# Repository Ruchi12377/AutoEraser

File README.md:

# 自動ホワイトボード消しの実用化に向けた改良

## 2022/12/13 第4版発行

---

# 目次

1. はじめに
   
   1. 概要
   
   2. 開発環境
   
   3. システムの概要

2. コンポーネント
   
   1. Camera
   
   2. Image
   
   3. KeystoneCorrection
   
   4. WhiteBoard (Feature)
   
   5. Select
   
   6. Erase (Feature)
   
   7. MoveInitial
   
   8. InitialSetting
   
   9. Pump
   
   10. Move (Feature)
   
   11. Serial

# 1.はじめに

## 1.概要

我々はRTミドルウェアを用いて、ホワイトボードの文字を自動で消すシステムを開発している。本稿では、本システムの改善について述べる。昨年のシステムとの相違点は主に三点ある。一つ目は、材質を木材からアルミニウムに変更することで歪みを解消し、スムーズな可動と軽量化を図ったことである。二つ目は消したい領域をより細かく指定可能にすることで、本来消すべきではない部分を消してしまうことを防げるようになったことである。三つ目は水が入ったタンクを設置し、自動で白板を濡らすことができるようになったため、雑巾を取り外して濡らす必要がなくなったことである。

自動ホワイトボード消しのイメージ

## 2.開発環境

本コンポーネント群の開発環境を以下に示す。

| OS       | Windows10                                 |
| -------- | ----------------------------------------- |
| RTミドルウェア | OpenRTM-aist-2.0.0-RELESE(Python 版)       |
| 開発環境     | VSCode                                    |
| Python   | 3.8.5                                     |
| 必要モジュール  | math, numpy, cv2, PIL, sys, time, tkinter |

## 3.システムの概要

このシステムは、ユーザーの指定した範囲もしくは、全範囲(全部消す)をレールや枠組みに沿って本体が移動し自動でホワイトボードに書かれたものを消すものである。

そして、制御部分にはRTミドルウェアを用いており、Cameraコンポーネントを用いて取得したホワイトボードの動画(画像)をSelectコンポーネントで消す範囲を選択し、Eraseコンポーネントでどのように移動するか決定することでMoveコンポーネントが移動するためのコマンドを生成し、Serialコンポーネントを用いてハードウェアに移動するデータをもちいて実際に動かす。というものである。

以下の2つのコンポーネント図を示す。

1.詳しく説明してあるコンポーネント図

2.簡潔化しまとまりごとに色分けしたコンポーネント図

# 2.コンポーネント

## 1.Camera

カメラから取得した画像を出力するコンポーネント。

コンフィギュレーションから使用するカメラのインデックスを設定することができる。

- **InPort**

- **OutPort**
  
  | **名称** | **データ型**         | **説明**            |
  | ------ | ---------------- | ----------------- |
  | image  | RTC::CameraImage | カメラから取得した画像を出力する。 |

- Configuration
  
  | 名称          | データ型  | 説明                   | 初期値 | 制限      |
  | ----------- | ----- | -------------------- | --- | ------- |
  | CameraIndex | short | 使用するカメラのインデックスを設定する。 | 0   | 0<=x<=5 |

## 2.Image

コンフィギュレーションで指定されたパスの画像をポートから出力するコンポーネント。

デバックする際、Cameraコンポーネントの代わりに使用することを想定している。

- **InPort**

- **OutPort**
  
  | 名称    | データ型             | 説明                           |
  | ----- | ---------------- | ---------------------------- |
  | Image | RTC::CameraImage | コンフィギュレーションで指定されたパスの画像を出力する。 |

- **Configuration**
  
  | 名称   | データ型   | 説明        | 初期値          | 制限        |
  | ---- | ------ | --------- | ------------ | --------- |
  | Path | string | 出力する画像のパス | Emprt String | Undefined |

## 3.KeystoneCorrection

台形補正をするコンポーネント。

GUIに画像が表示されており、4隅をクリックすることで台形補正を行う。

ホワイトボードをカメラで撮影しなぞるようにして選択するが、その際ホワイトボードの画像は斜めになっているのでこのコンポーネントが必要。

- **InPort**

| 名称      | データ型             | 説明        |
| ------- | ---------------- | --------- |
| ImageIn | RTC::CameraImage | 台形補正をする画像 |

- **OutPort**

| 名称       | データ型             | 説明        |
| -------- | ---------------- | --------- |
| ImageOut | RTC::CameraImage | 台形補正済みの画像 |

- **Configuration**

## 4.WhiteBoard (Feature)

実装予定

## 5.Select

範囲選択をし、選択した矩形の座標を出力するコンポーネント。

選択範囲を左上を基準とし0~1で表す。真ん中から右下まで選択した場合、Start = (0.5, 0.5) End = (1, 1)となる。

**Camera** **Image** **Select** の3つに加え画像切り取りコンポーネントを作成することで画像切り取りができるコンポーネント群をかんたんに作れる。

- **InPort**
  
  | 名称            | データ型        | 説明          |
  | ------------- | ----------- | ----------- |
  | ShowImage     | CameraImage | 選択する際の背景の画像 |
  | CompeteMotion | TimedString | 終了した動作名     |
  | StatusCode    | TimedUShort | ステータスコード    |

- **OutPort**
  
  | 名称       | データ型              | 説明         |
  | -------- | ----------------- | ---------- |
  | StartPos | RTC::TimedPoint2D | 指定された範囲の始点 |
  | EndPos   | RTC::TimedPoint2D | 指定された範囲の終点 |

- **Configuration**
  
  | 名称     | データ型 | 説明         | 初期値 | 制限           |
  | ------ | ---- | ---------- | --- | ------------ |
  | Width  | int  | 選択ウィンドウの横幅 | 800 | 400<=x<=1600 |
  | Height | int  | 選択ウィンドウの高さ | 450 | 225<=x<=900  |

## 5.Erase (Feature)

選択された範囲を元に消すためのパスを決定するコンポーネント。

- **InPort**
  
  | 名称       | データ型              | 説明         |
  | -------- | ----------------- | ---------- |
  | StartPos | RTC::TimedPoint2D | 指定された範囲の始点 |
  | EndPos   | RTC::TimedPoint2D | 指定された範囲の終点 |

- **OutPort**
  
  | 名称       | データ型           | 説明                         |
  | -------- | -------------- | -------------------------- |
  | MovePath | TimedStringSeq | **x:y**の形式で移動する座標のデータを出力する |

- **Configuration**
  
  | 名称  | データ型 | 説明  | 初期値 | 制限  |
  | --- | ---- | --- | --- | --- |
  |     |      |     |     |     |

## 5.MoveInitial

初期位置(左上)に本体を移動させるコンポーネント。

移動しきったかの検出にはリミットスイッチを用いる。

- **InPort**
  
  | 名称            | データ型      | 説明              |
  | ------------- | --------- | --------------- |
  | MoveToInitial | RTC::Time | 初期位置に戻るタイミングを指定 |

- **OutPort**
  
  | 名称      | データ型             | 説明                |
  | ------- | ---------------- | ----------------- |
  | Command | RTC::TimedString | 初期位置に戻るためのコマンドを生成 |

- **Configuration**
  
  | 名称      | データ型 | 説明               | 初期値 | 制限        |
  | ------- | ---- | ---------------- | --- | --------- |
  | TimeOut | int  | 移動完了せずタイムアウトする時間 | -1  | -1<=x<=60 |

## 6.InitialSetting

本体のサイズ、ホワイトボードの横幅をリミットスイッチを用いて検出するコンポーネント。

単位はステッピングモーターの回転数。

- **InPort**
  
  | 名称      | データ型      | 説明        |
  | ------- | --------- | --------- |
  | Setting | RTC::Time | 検出するタイミング |

- **OutPort**
  
  | 名称      | データ型             | 説明                |
  | ------- | ---------------- | ----------------- |
  | Command | RTC::TimedString | 初期設定を行うためのコマンドを生成 |

- **Configuration**
  
  | 名称  | データ型 | 説明  | 初期値 | 制限  |
  | --- | ---- | --- | --- | --- |
  |     |      |     |     |     |

## 7.Pump

指定された量の水をポンプから出すコンポーネント。

単位はmL

- **InPort**
  
  | 名称          | データ型             | 説明         |
  | ----------- | ---------------- | ---------- |
  | WaterAmount | RTC::TimedUShort | ポンプから出す水の量 |

- **OutPort**
  
  | 名称              | データ型             | 説明               |
  | --------------- | ---------------- | ---------------- |
  | PumpWaterAmount | RTC::TimedString | ポンプから水を出すためのコマンド |

- **Configuration**
  
  | 名称   | データ型 | 説明  | 初期値 | 制限  |
  | ---- | ---- | --- | --- | --- |
  | Amou |      |     |     |     |

## 8.Move (Feature)

パスを元に、モーターを動かすためのコマンドを生成するコンポーネント。

- **InPort**
  
  | 名称      | データ型              | 説明            |
  | ------- | ----------------- | ------------- |
  | Command | RTC::TimedPoint2D | モーターを動かすための座標 |

- **OutPort**
  
  | 名称      | データ型             | 説明              |
  | ------- | ---------------- | --------------- |
  | Command | RTC::TimedString | ハードウェアに送信するコマンド |

- **Configuration**
  
  | 名称  | データ型 | 説明  | 初期値 | 制限  |
  | --- | ---- | --- | --- | --- |
  |     |      |     |     |     |

## 9.Serial

シリアル通信のRead/Writeを行うコンポーネント。

- **InPort**
  
  | 名称    | データ型             | 説明             |
  | ----- | ---------------- | -------------- |
  | Write | RTC::TimedString | シリアル通信で書き込むデータ |

- **OutPort**
  
  | 名称   | データ型             | 説明              |
  | ---- | ---------------- | --------------- |
  | Read | RTC::TimedString | シリアル通信で読み込んだデータ |

- **Configuration**
  
  | 名称        | データ型   | 説明               | 初期値         | 制限        |
  | --------- | ------ | ---------------- | ----------- | --------- |
  | Path      | string | シリアル通信を行うデバイスのパス | EmptyString |           |
  | Boundrate | int    | シリアル通信を行うための速度   | 9600        | Undefined |

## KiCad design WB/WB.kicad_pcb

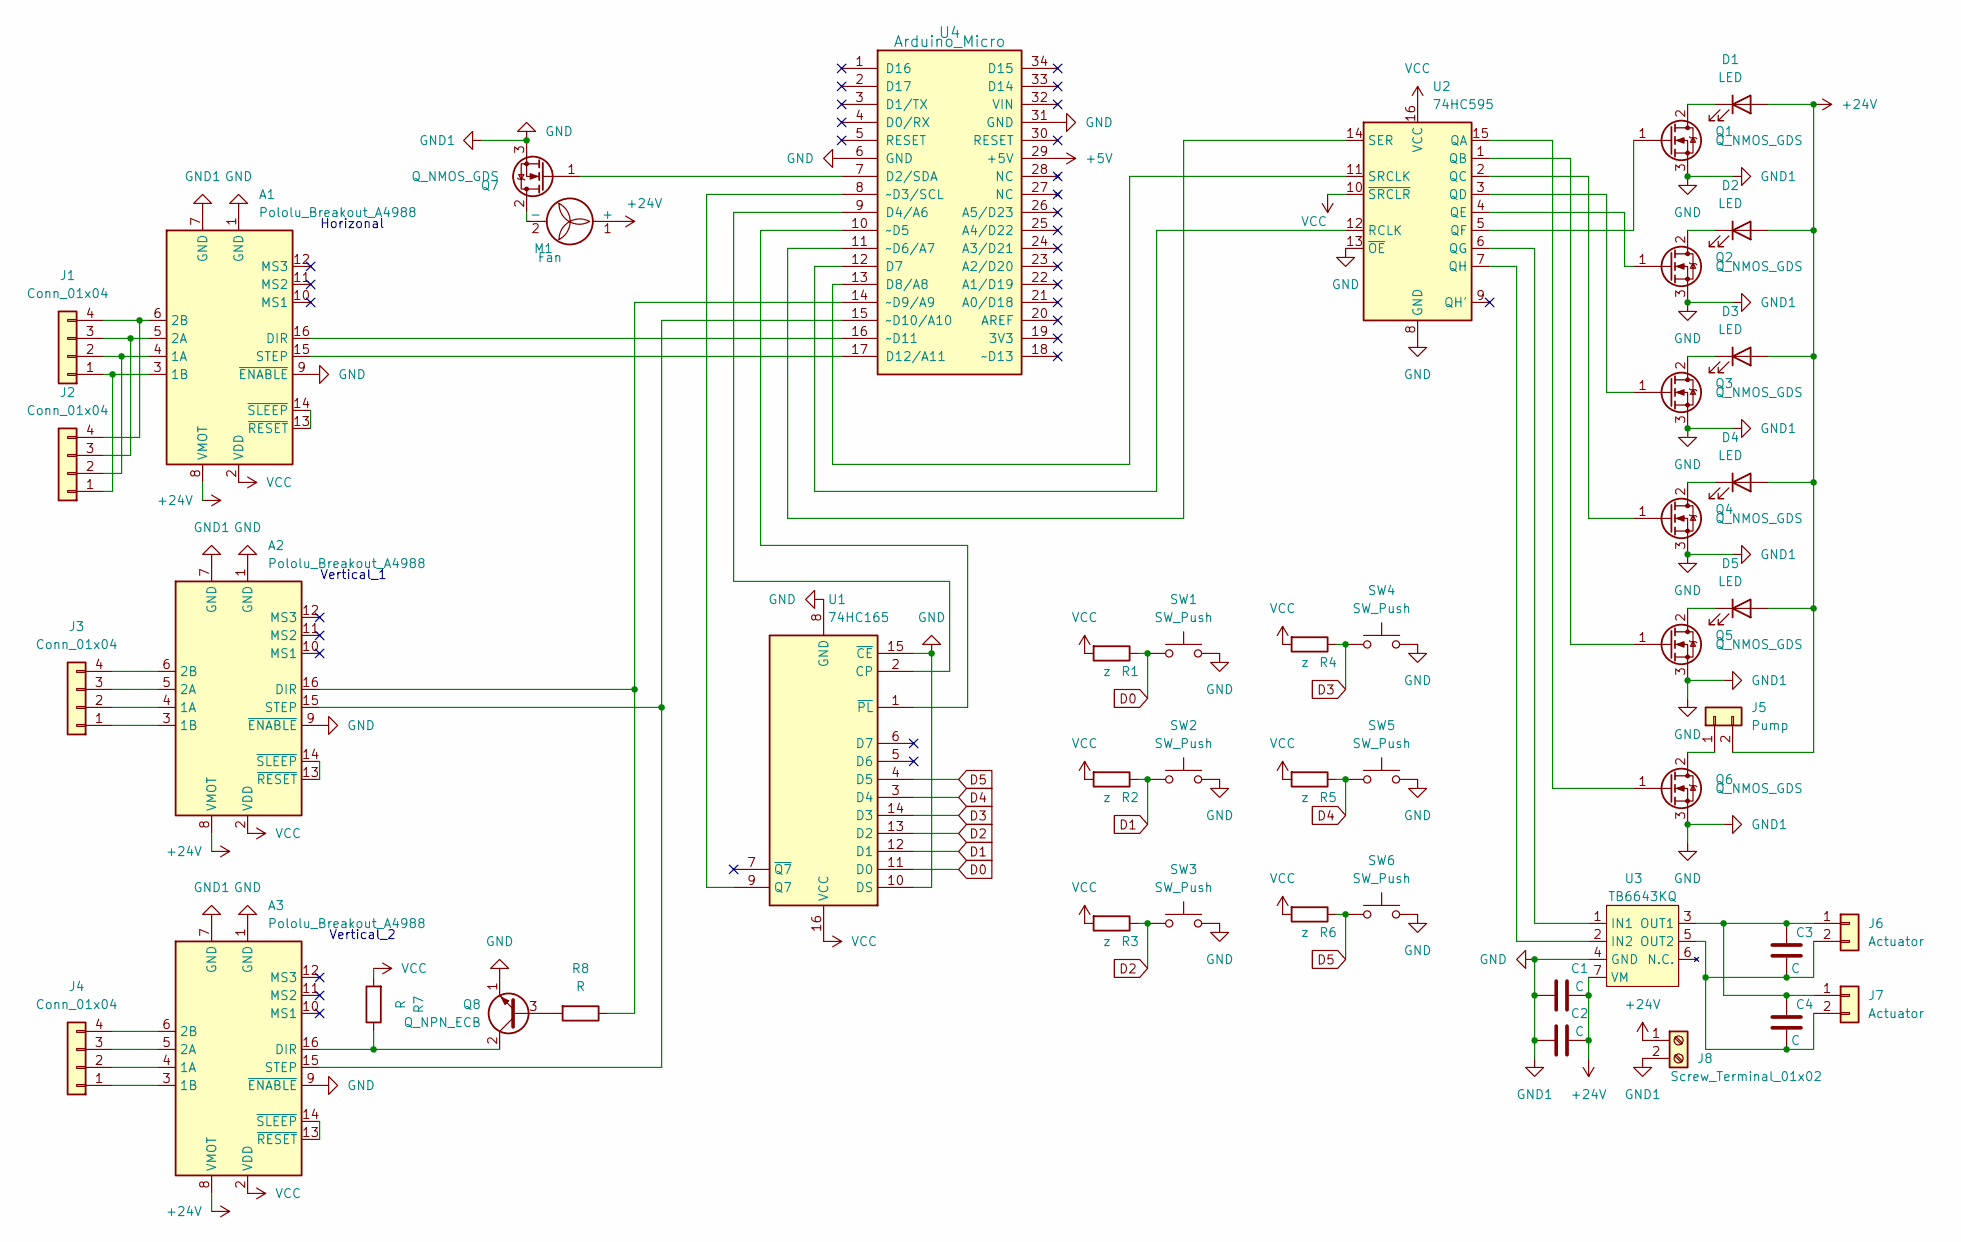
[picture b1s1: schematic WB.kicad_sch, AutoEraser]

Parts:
A1, A2, A3: Pololu_Breakout_A4988; MODULE_A4988_STEPPER_MOTOR_DRIVER_CARRIER
C1, C3, C4: C; C_Rect_L4.0mm_W2.5mm_P2.50mm
C2: C; C_Radial_D8.0mm_H11.5mm_P3.50mm
D1, D2, D3, D4, D5: LED; PinHeader_1x02_P2.54mm_Vertical
J1, J2, J3, J4: Conn_01x04; PinHeader_1x04_P2.54mm_Vertical
J5: Pump; PinHeader_1x02_P2.54mm_Vertical
J6, J7: Actuator; PinHeader_1x02_P2.54mm_Vertical
J8: Screw_Terminal_01x02; TerminalBlock_bornier-2_P5.08mm
M1: Fan; PinHeader_1x02_P2.54mm_Vertical
Q1, Q2, Q3, Q4, Q5, Q6, Q7: Q_NMOS_GDS; TO254P1054X470X1955-3
Q8: Q_NPN_ECB; TO-92L_Inline_Wide
R1, R2, R3, R4, R5, R6: z; R_Box_L8.4mm_W2.5mm_P5.08mm
R7, R8: R; R_Box_L8.4mm_W2.5mm_P5.08mm
SW1, SW2, SW3, SW4, SW5, SW6: SW_Push; PinHeader_1x02_P2.54mm_Vertical
U1: 74HC165; DIP-16_W7.62mm
U2: 74HC595; DIP-16_W7.62mm
U3: TB6643KQ; SIP1005W50P254L1965H1265Q7
U4: Arduino_Micro

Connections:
+24V: A1.8 (VMOT), A2.8 (VMOT), A3.8 (VMOT), C1.2, C2.2, D1.2 (A), D2.2 (A), D3.2 (A), D4.2 (A), D5.2 (A), J5.2, J8.1, M1.1 (+), U3.7 (VM)
D0: R1.1, SW1.1, U1.11 (D0)
D1: R2.1, SW2.1, U1.12 (D1)
D2: R3.1, SW3.1, U1.13 (D2)
D3: R4.1, SW4.1, U1.14 (D3)
D4: R5.1, SW5.1, U1.3 (D4)
D5: R6.1, SW6.1, U1.4 (D5)
GND: A1.1 (GND), A1.7 (GND), A2.1 (GND), A2.7 (GND), A2.9 (~ENABLE), A3.1 (GND), A3.7 (GND), A3.9 (~ENABLE), C1.1, C2.1, J8.2, Q1.3 (S), Q2.3 (S), Q3.3 (S), Q4.3 (S), Q5.3 (S), Q6.3 (S), Q7.3 (S), Q8.1 (E), SW1.2, SW2.2, SW3.2, SW4.2, SW5.2, SW6.2, U1.8 (GND), U1.10 (DS), U1.15 (~CE), U2.8 (GND), U2.13 (~OE), U3.4 (GND), U4.6 (GND), U4.31 (GND); also elsewhere on the board
unnamed: A1.3 (1B), J1.1, J2.1
unnamed: A1.4 (1A), J1.2, J2.2
unnamed: A1.5 (2A), J1.3, J2.3
unnamed: A1.6 (2B), J1.4, J2.4
unnamed 12: A1.9 (~ENABLE); also elsewhere on the board
unnamed: A1.13 (~RESET), A1.14 (~SLEEP)
unnamed 14: A1.15 (STEP), U4.17 (D12/A11); also elsewhere on the board
unnamed 15: A1.16 (DIR), U4.16 (~D11); also elsewhere on the board
unnamed: A2.3 (1B), J3.1
unnamed: A2.4 (1A), J3.2
unnamed: A2.5 (2A), J3.3
unnamed: A2.6 (2B), J3.4
unnamed: A2.13 (~RESET), A2.14 (~SLEEP)
unnamed 21: A2.15 (STEP), A3.15 (STEP), U4.15 (~D10/A10); also elsewhere on the board
unnamed 22: A2.16 (DIR), R8.1, U4.14 (~D9/A9); also elsewhere on the board
unnamed: A3.3 (1B), J4.1
unnamed: A3.4 (1A), J4.2
unnamed: A3.5 (2A), J4.3
unnamed: A3.6 (2B), J4.4
unnamed: A3.13 (~RESET), A3.14 (~SLEEP)
unnamed: A3.16 (DIR), Q8.2 (C), R7.1
unnamed: D1.1 (K), Q1.2 (D)
unnamed: D2.1 (K), Q2.2 (D)
unnamed: D3.1 (K), Q3.2 (D)
unnamed: D4.1 (K), Q4.2 (D)
unnamed: D5.1 (K), Q5.2 (D)
unnamed: J5.1, Q6.2 (D)
unnamed: C3.1, C4.1, J6.1, J7.1, U3.3 (OUT1)
unnamed: C3.2, C4.2, J6.2, J7.2, U3.5 (OUT2)
unnamed: M1.2 (-), Q7.2 (D)
unnamed: Q1.1 (G), U2.5 (QF)
unnamed: Q2.1 (G), U2.4 (QE)
unnamed: Q3.1 (G), U2.3 (QD)
unnamed: Q4.1 (G), U2.2 (QC)
unnamed: Q5.1 (G), U2.1 (QB)
unnamed: Q6.1 (G), U2.15 (QA)
unnamed: Q7.1 (G), U4.7 (D2/SDA)
unnamed: Q8.3 (B), R8.2
unnamed: U1.1 (~PL), U4.10 (~D5)
unnamed: U1.2 (CP), U4.9 (D4/A6)
unnamed: U1.9 (Q7), U4.8 (~D3/SCL)
unnamed: U2.6 (QG), U3.1 (IN1)
unnamed: U2.7 (QH), U3.2 (IN2)
unnamed: U2.11 (SRCLK), U4.13 (D8/A8)
unnamed: U2.12 (RCLK), U4.12 (D7)
unnamed: U2.14 (SER), U4.11 (~D6/A7)
VCC: A1.2 (VDD), A2.2 (VDD), A3.2 (VDD), R1.2, R2.2, R3.2, R4.2, R5.2, R6.2, R7.2, U1.16 (VCC), U2.10 (~SRCLR), U2.16 (VCC); also elsewhere on the board

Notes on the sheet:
Vertical_2
Vertical_1
Horizonal

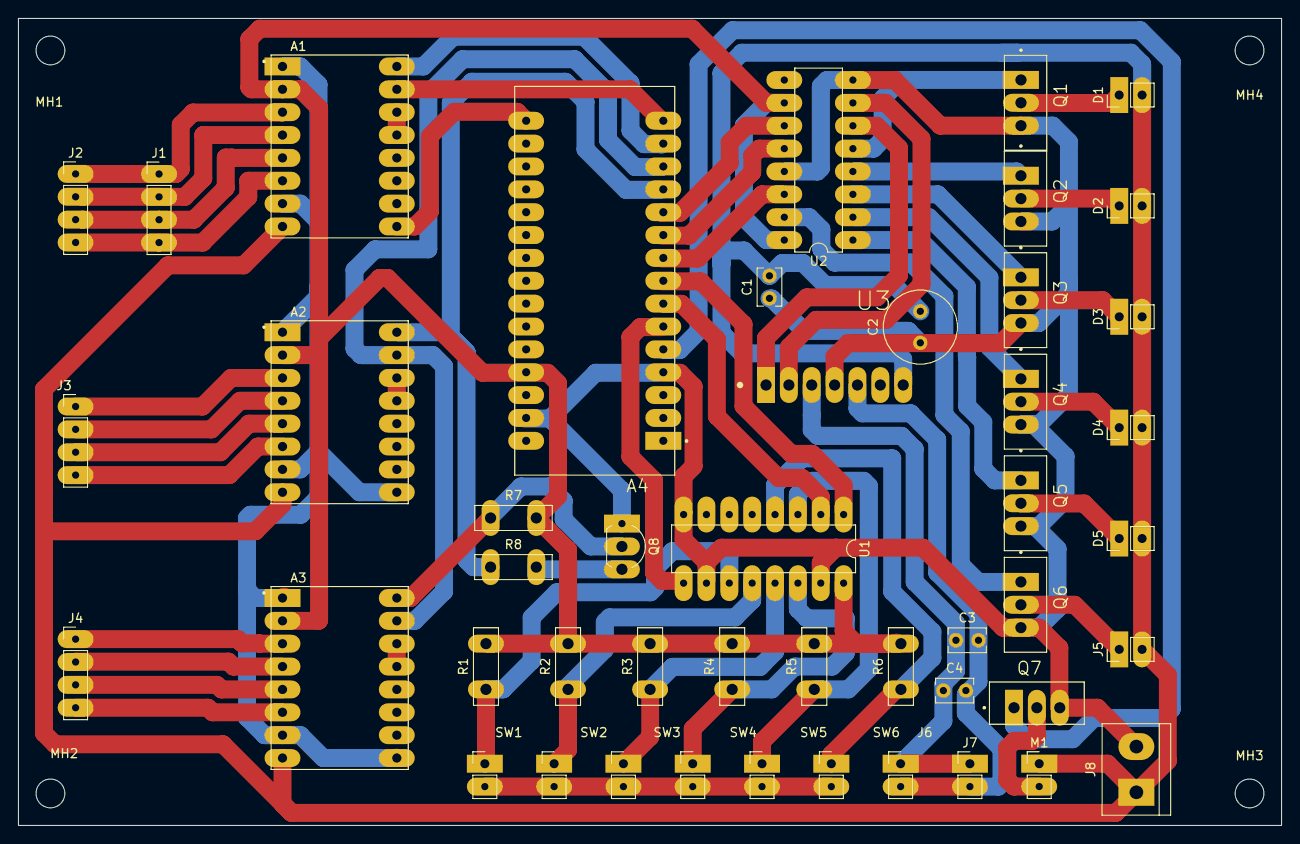
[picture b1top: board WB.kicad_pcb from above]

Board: 2 copper layers, 140.3 x 89.7 mm, 51 parts (0 on the bottom side), 48 nets.

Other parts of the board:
A4: Arduino_Micro; SHIELD_ARDUINO_NANO
MH1, MH2, MH3, MH4: MountingHole_3.2mm_M3

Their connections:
GND: A4.4 (GND), A4.29 (GND); also elsewhere on the board
unnamed 12: A4.16 (D13); also elsewhere on the board
unnamed 14: A4.15 (D12); also elsewhere on the board
unnamed 15: A4.14 (D11); also elsewhere on the board
unnamed 21: A4.13 (D10); also elsewhere on the board
unnamed 22: A4.12 (D9); also elsewhere on the board
VCC: A4.27 (+5V); also elsewhere on the board

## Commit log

2022-08-07 Camera
2022-08-07 Selectコンポーネントを作成
2022-08-07 show img
2022-08-07 コメントを追加
2022-08-08 check if input is "is not None"
2022-08-08 edit conf
2022-08-08 show img with tkinter
2022-08-08 keystone correction
2022-08-08 write out time & data
2022-08-08 create erase component
2022-08-09 setTimestamp
2022-08-21 bug fix
    deactivateした後にactivateするとエラーになるバグを修正
2022-08-21 set conf
2022-08-22 -f option
2022-09-28 move to folder
2022-10-11 space x 4 to tab
2022-10-23 1st edition
2022-10-23 重複部分を修正
2022-10-29 about Select
2022-10-30 バージョン情報を追加
2022-10-31 Selectの説明
2022-10-31 ステッピングモーターライブラリ
2022-10-31 制御プログラム
2022-10-31 表を追加
2022-10-31 各コンポーネントの説明を追加
2022-10-31 目次を編集
2022-10-31 図の位置の変更と、各コンポーネント説明の文末を追加
2022-11-02 回路図を追加
2022-11-02 ignore dsstore
2022-11-02 Serialコンポーネントを追加
2022-11-02 バグ修正とバッチファイル
2022-11-03 Serial通信
2022-11-03 シリアル通信テスト用文字入力コンポーネント
2022-11-03 画像の追加とリンクを修正
2022-11-04 serial read
2022-11-04 Selectのコードを再生成しバグ修正
2022-11-07 ファン、アクチュエーターを追加。配置を修正
2022-11-08 配線の修正
2022-11-08 ICのDIPを変更。
2022-11-09 配線の太さを太く
2022-11-09 不要なファイルの削除
2022-11-10 配線がかぶっていたところを修正
2022-11-12 パッドのサイズを変更したが、だめ
2022-11-13 配線しやすいように回路を変更
2022-11-17 メインマイコンの変更
2022-11-17 台形補正コンポーネント
2022-11-18 ホワイトボード操作コンポーネントを追加
2022-11-18 詳細のコンポーネント図の修正
2022-11-18 背景を透明に
2022-11-18 差し替え
2022-11-18 ポンプとmoveini
    ポンプとmoveini
2022-11-18 moveinitial
2022-11-18 erase
2022-11-18 new-erase
2022-11-18 スペースや改行を修正
2022-11-18 コンポーネント図の修正。ホワイトボード操作コンポーネントの追加
2022-11-18 コンポーネント説明の追加
2022-12-05 バッチファイルの追加。不要ファイルの削除
2022-12-05 回路図の修正
2022-12-13 台形補正の修正
    台形補正の修正（変数名、フォーマット、コンフィグ変数）
2022-12-13 台形補正の修正の修正の修正
2022-12-13 説明文の追加
2022-12-13 台形補正の修正の以下略
2022-12-13 構成するものを図で表した
2023-04-18 回路周りのファイル
